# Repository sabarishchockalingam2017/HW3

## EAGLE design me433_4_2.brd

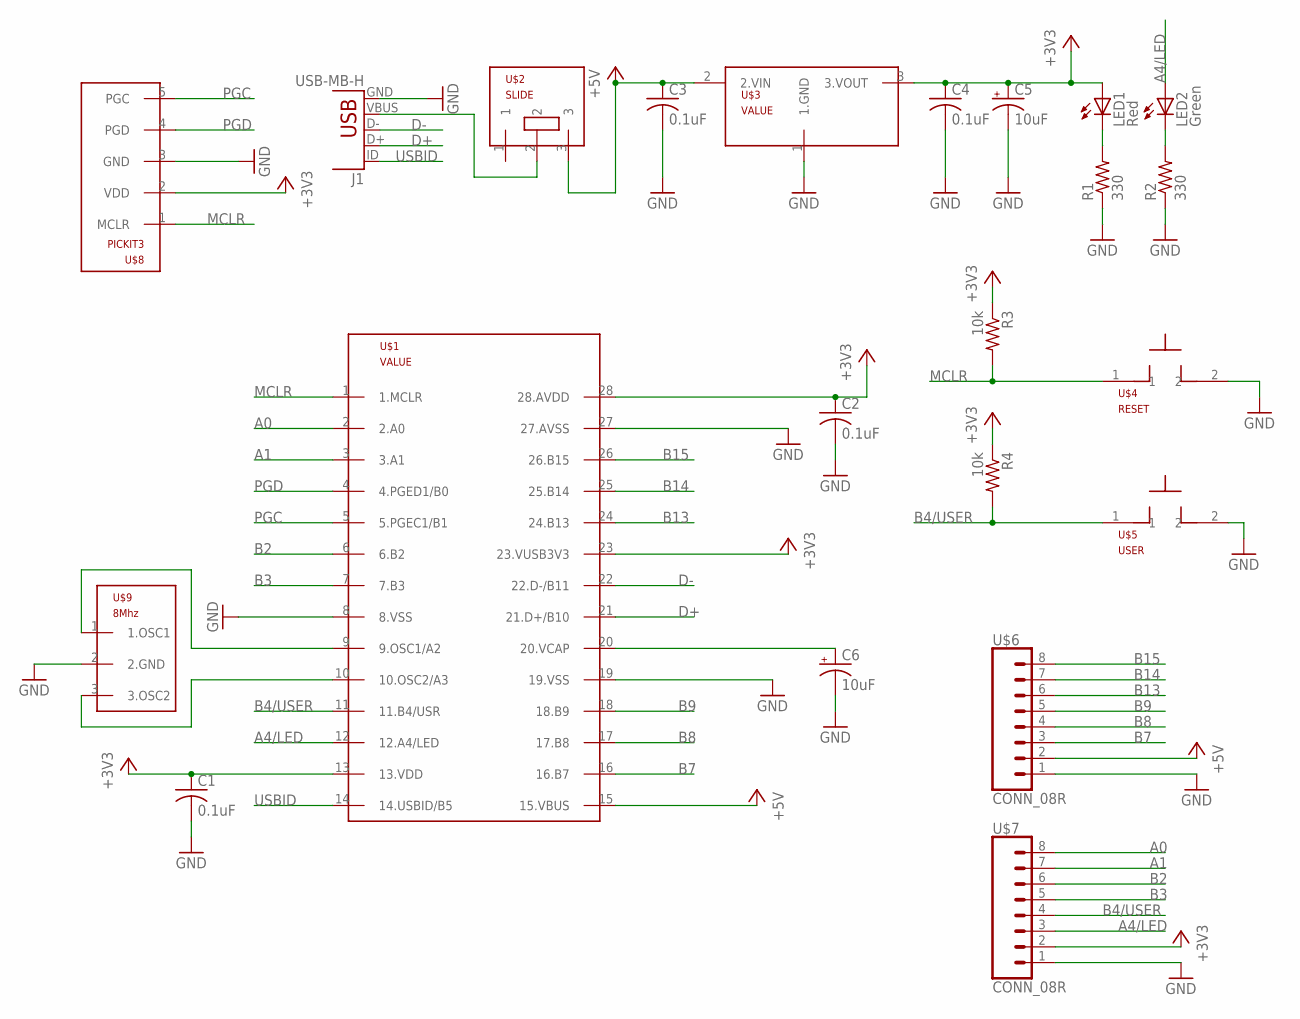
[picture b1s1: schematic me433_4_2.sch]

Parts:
C1, C2, C3, C4: 0.1uF; C025-025X050
C5, C6: 10uF; B45181B
J1: USB-MB-H
LED1: Red; LED3MM
LED2: Green; LED3MM
R1, R2: 330; 0207/10
R3, R4: 10k; 0207/10
U$1: PIC32MX250F128B; DIL28-3
U$2: SLIDE
U$3: MCP1702; TO92
U$4: RESET; PB
U$5: USER; PB
U$6, U$7: CONN_08R; 1X08
U$8: PICKIT3; 1X05
U$9: 8Mhz; OSC

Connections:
+3V3: C1.1, C2.1, C4.1, C5.+, LED1.A, R3.1, R4.1, U$1.13 (13.VDD), U$1.23 (23.VUSB3V3), U$1.28 (28.AVDD), U$3.3 (3.VOUT), U$7.2, U$8.2 (VDD)
+5V: C3.1, U$1.15 (15.VBUS), U$2.3, U$3.2 (2.VIN), U$6.2
A0: U$1.2 (2.A0), U$7.8
A1: U$1.3 (3.A1), U$7.7
A4/LED: LED2.A, U$1.12 (12.A4/LED), U$7.3
B2: U$1.6 (6.B2), U$7.6
B3: U$1.7 (7.B3), U$7.5
B4/USER: R4.2, U$1.11 (11.B4/USR), U$5.1, U$7.4
B7: U$1.16 (16.B7), U$6.3
B8: U$1.17 (17.B8), U$6.4
B9: U$1.18 (18.B9), U$6.5
B13: U$6.6
B14: U$1.25 (25.B14), U$6.7
B15: U$1.26 (26.B15), U$6.8
D+: J1.D+, U$1.21 (21.D+/B10)
D-: J1.D-, U$1.22 (22.D-/B11)
GND: C1.2, C2.2, C3.2, C4.2, C5.-, C6.-, J1.GND, R1.1, R2.1, U$1.8 (8.VSS), U$1.19 (19.VSS), U$1.27 (27.AVSS), U$3.1 (1.GND), U$4.2, U$5.2, U$6.1, U$7.1, U$8.3 (GND), U$9.2 (2.GND)
MCLR: R3.2, U$1.1 (1.MCLR), U$4.1, U$8.1 (MCLR)
unnamed: J1.VBUS, U$2.2
unnamed: U$1.9 (9.OSC1/A2), U$9.1 (1.OSC1)
unnamed: LED1.K (C), R1.2
unnamed: LED2.K (C), R2.2
unnamed: U$1.10 (10.OSC2/A3), U$9.3 (3.OSC2)
unnamed: C6.+, U$1.20 (20.VCAP)
PGC: U$1.5 (5.PGEC1/B1), U$8.5 (PGC)
PGD: U$1.4 (4.PGED1/B0), U$8.4 (PGD)
USBID: J1.ID, U$1.14 (14.USBID/B5)

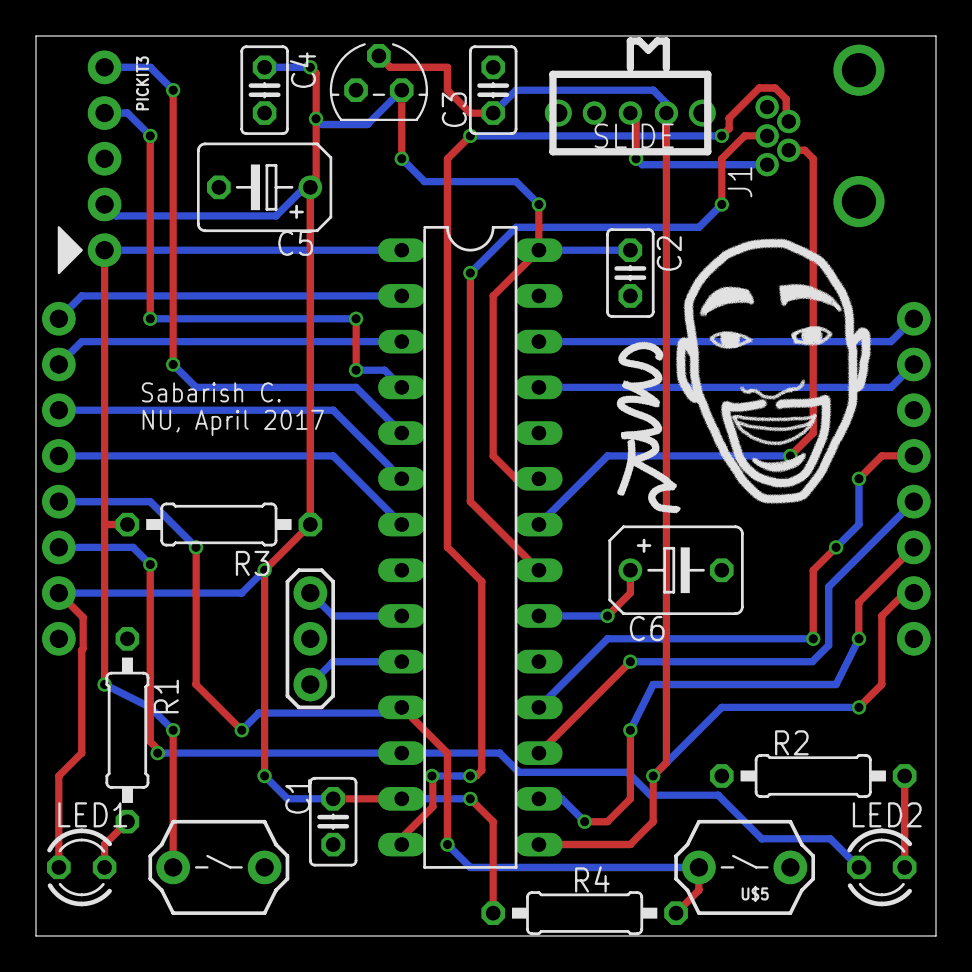
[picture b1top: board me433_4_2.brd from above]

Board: 2 copper layers, 50.0 x 50.0 mm, 22 parts (0 on the bottom side), 26 nets.

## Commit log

2017-04-07 Gerber Files
2017-04-09 second upload
    adding brd and sch. files
